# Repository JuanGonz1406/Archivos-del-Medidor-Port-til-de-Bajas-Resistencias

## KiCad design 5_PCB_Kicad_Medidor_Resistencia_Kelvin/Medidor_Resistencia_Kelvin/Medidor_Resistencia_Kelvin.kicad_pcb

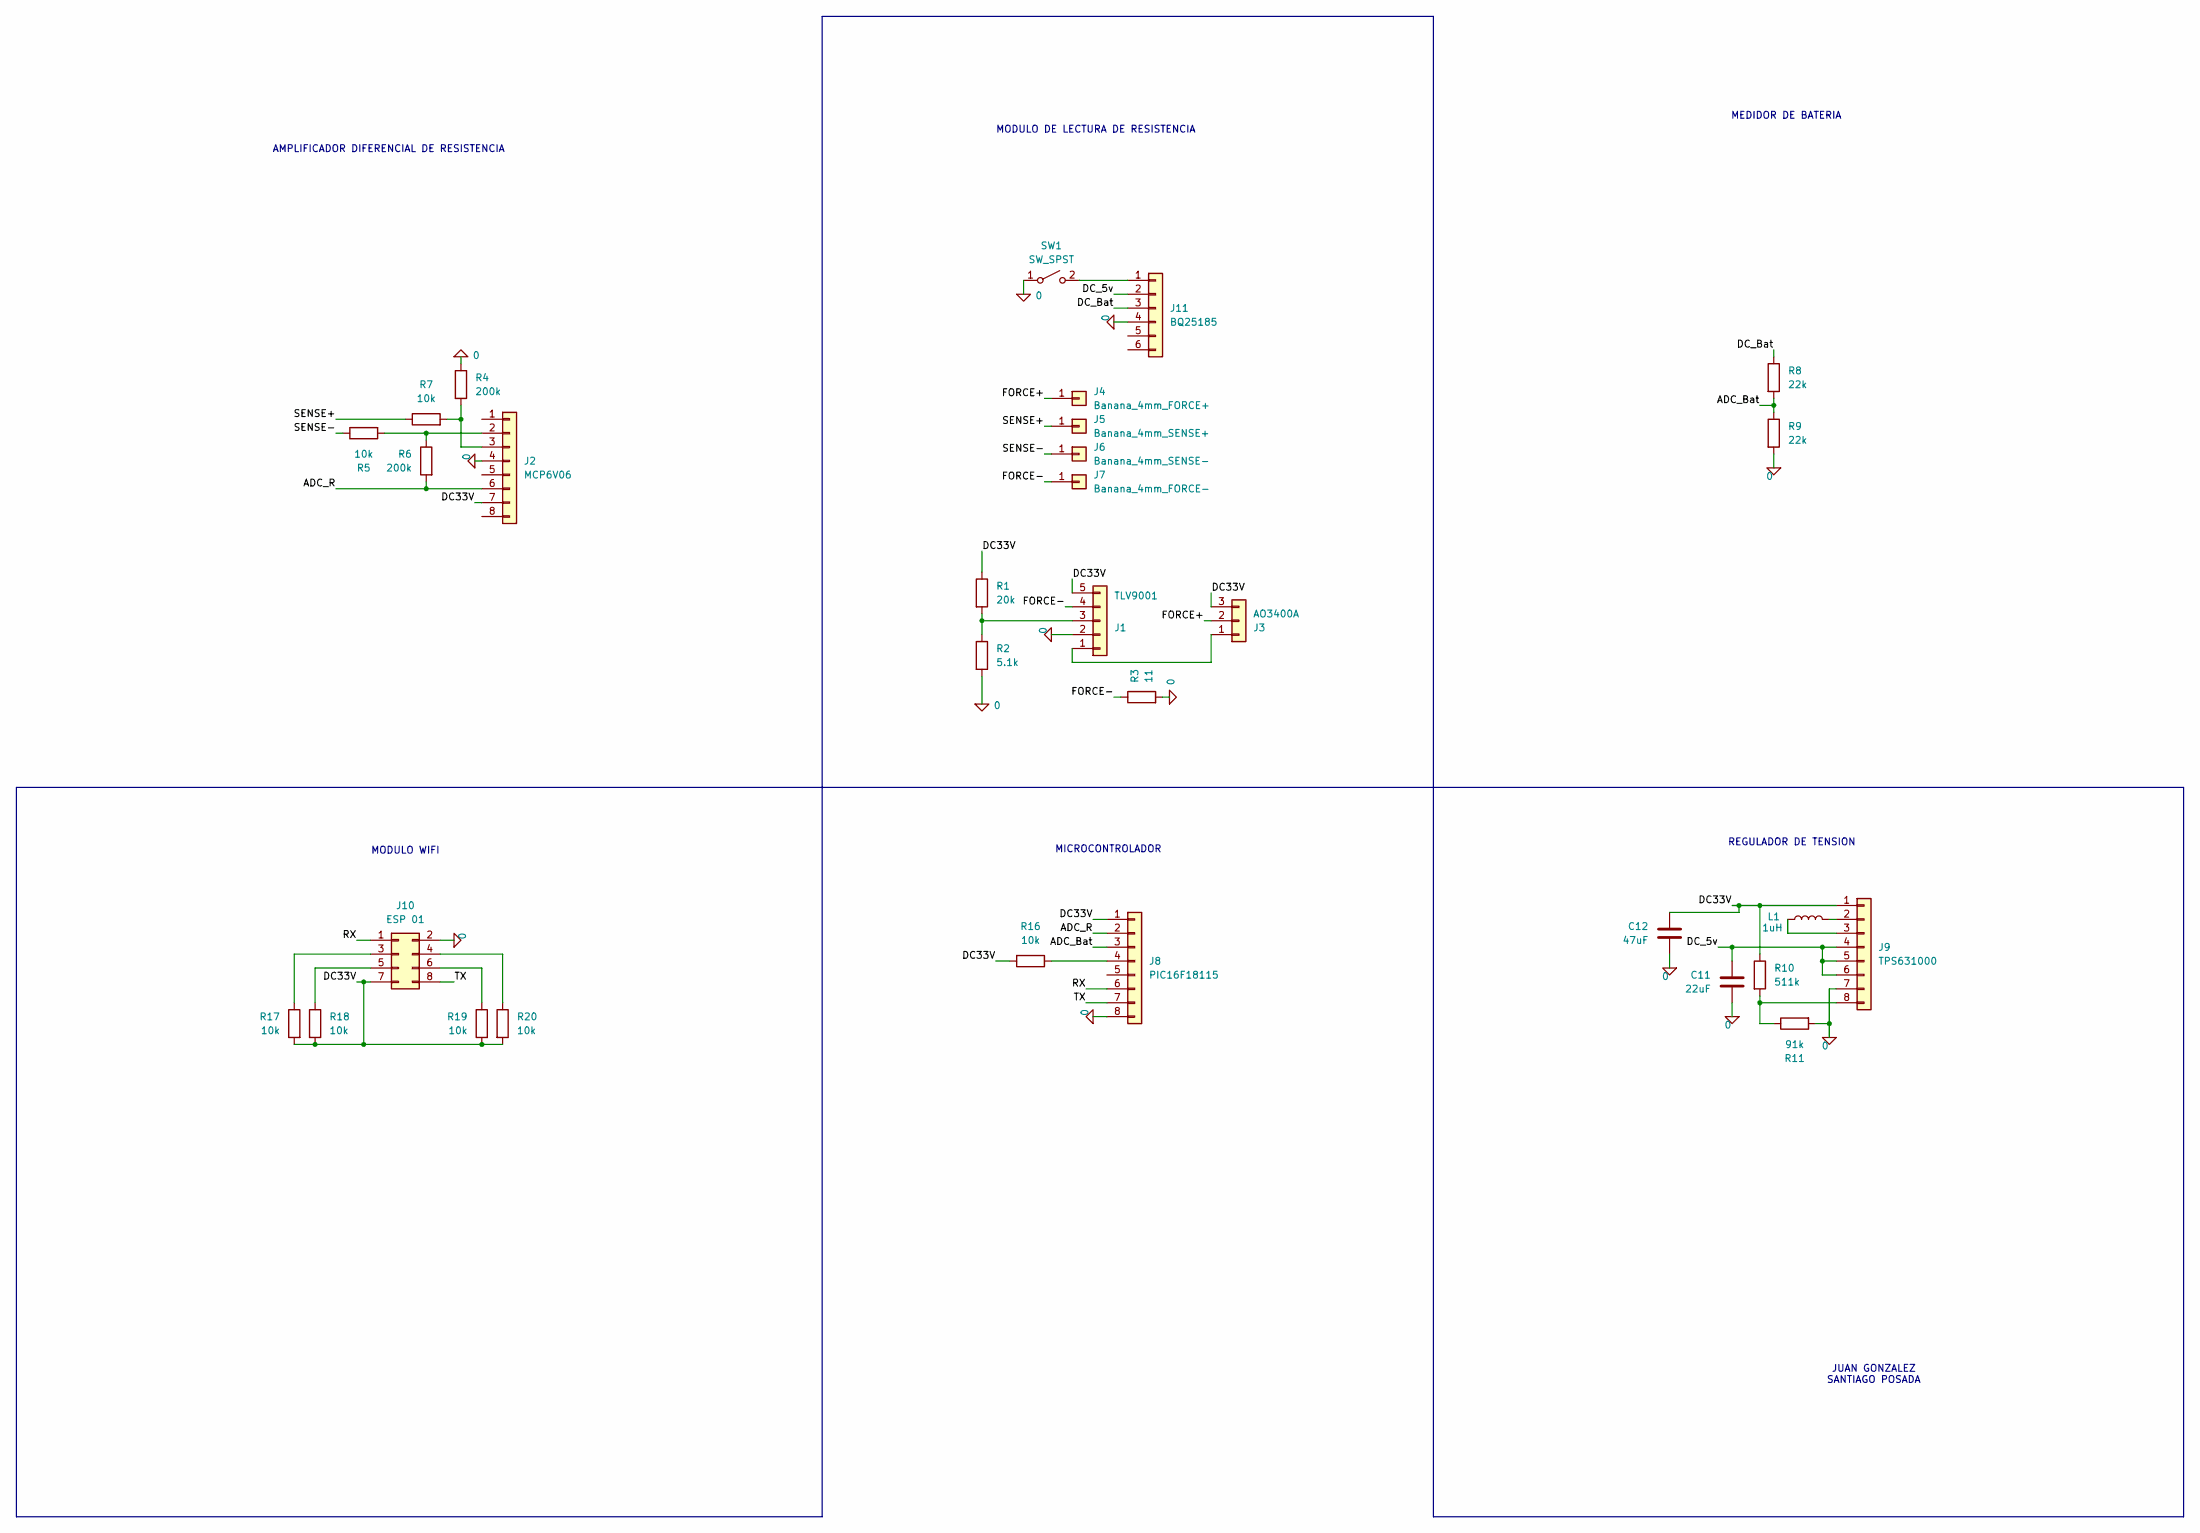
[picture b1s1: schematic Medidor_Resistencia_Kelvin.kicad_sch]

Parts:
C11: 22uF; C_1206_3216Metric
C12: 47uF; C_1206_3216Metric
J1: TLV9001; SOT-23-5
J2: MCP6V06; SOIC-8_3.9x4.9mm_P1.27mm
J3: AO3400A; SOT-23
J4: Banana_4mm_FORCE+; Banana4mm
J5: Banana_4mm_SENSE+; Banana4mm
J6: Banana_4mm_SENSE-; Banana4mm
J7: Banana_4mm_FORCE-; Banana4mm
J8: PIC16F18115; SOIC-8_3.9x4.9mm_P1.27mm
J9: TPS631000; SOT-583-8
J10: ESP 01; PinSocket_2x04_P2.54mm_Vertical
J11: BQ25185; PinHeader_1x06_P2.54mm_Vertical
L1: 1uH; L_Wuerth_MAPI-2512
R1: 20k; R_1206_3216Metric
R2: 5.1k; R_1206_3216Metric
R3: 11; R_1206_3216Metric
R4, R6: 200k; R_1206_3216Metric
R5, R7, R16, R17, R18, R19, R20: 10k; R_1206_3216Metric
R8, R9: 22k; R_1206_3216Metric
R10: 511k; R_1206_3216Metric
R11: 91k; R_1206_3216Metric
SW1: SW_SPST; SW_E-Switch_EG1224_SPDT_Angled

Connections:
0: C11.2, C12.2, J1.2, J2.4, J8.8, J9.7, J10.2, J11.4, R2.2, R3.2, R4.1, R9.2, R11.2, SW1.1 (A)
/ADC_Bat: J8.3, R8.2, R9.1
/ADC_R: J2.6, J8.2, R6.2
/DC33V: C12.1, J1.5, J2.7, J3.3, J8.1, J9.1, J10.7, R1.1, R10.1, R16.2, R17.2, R18.2, R19.2, R20.2
/DC_5v: C11.1, J9.4, J9.5, J9.6, J11.2
/DC_Bat: J11.3, R8.1
/FORCE+: J3.2, J4.1 (Pin_1_1)
/FORCE-: J1.4, J7.1 (Pin_1_1), R3.1
/RX: J8.6, J10.1
/SENSE+: J5.1 (Pin_1_1), R7.1
/SENSE-: J6.1 (Pin_1_1), R5.1
/TX: J8.7, J10.8
unnamed: J1.1, J3.1
unnamed: J1.3, R1.2, R2.1
unnamed: J2.2, R5.2, R6.1
unnamed: J2.3, R4.2, R7.2
unnamed: J8.4, R16.1
unnamed: J9.2, L1.2
unnamed: J9.3, L1.1
unnamed: J9.8, R10.2, R11.1
unnamed: J10.3, R17.1
unnamed: J10.4, R20.1
unnamed: J10.5, R18.1
unnamed: J10.6, R19.1
unnamed: J11.1, SW1.2 (B)

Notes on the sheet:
MEDIDOR DE BATERIA
MICROCONTROLADOR
MODULO WIFI
AMPLIFICADOR DIFERENCIAL DE RESISTENCIA
REGULADOR DE TENSION
MODULO DE LECTURA DE RESISTENCIA
JUAN GONZALEZ SANTIAGO POSADA

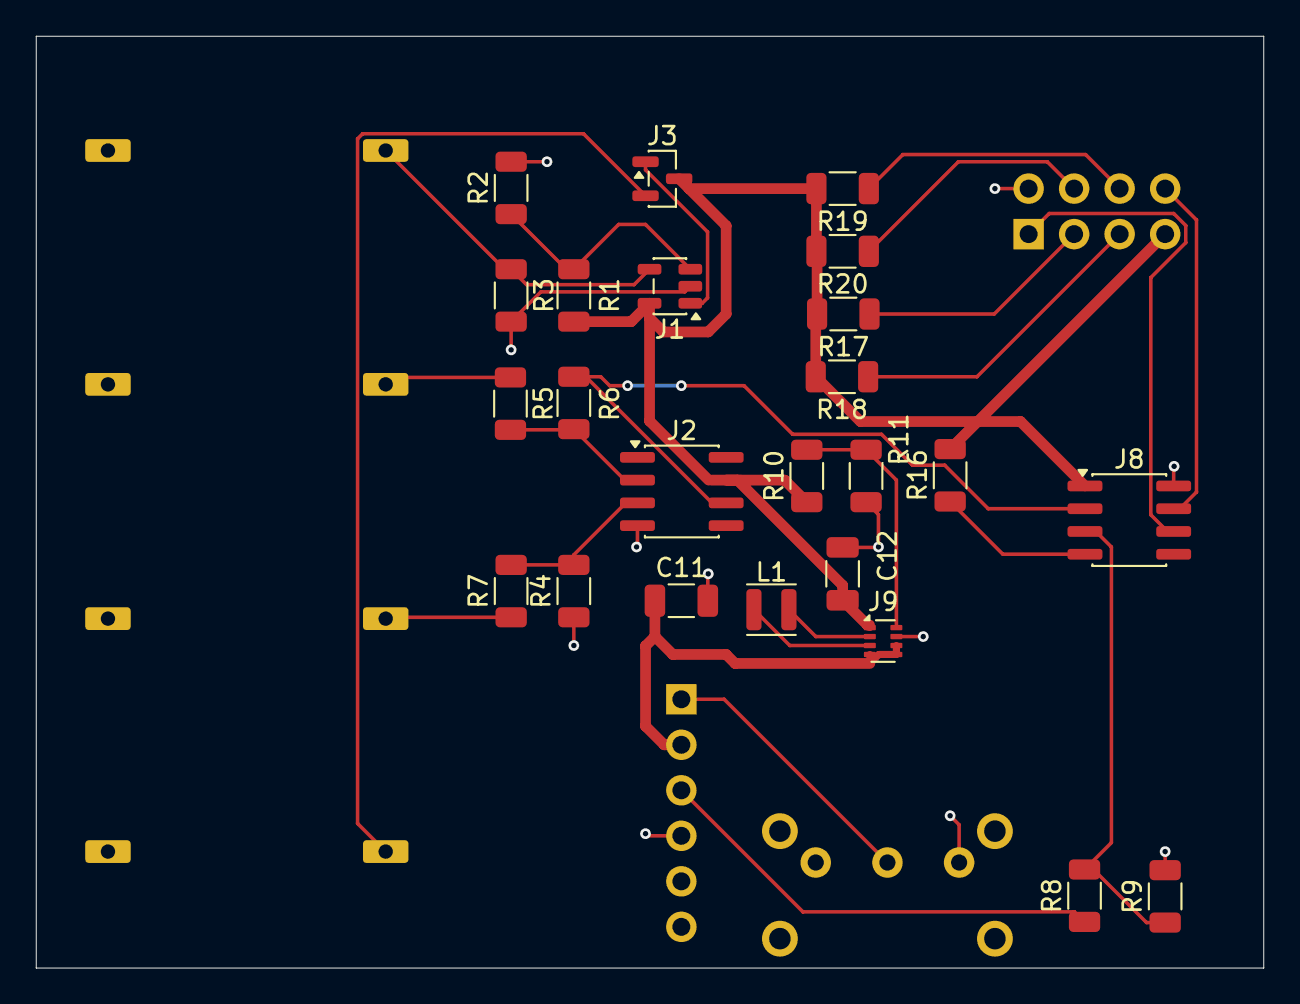
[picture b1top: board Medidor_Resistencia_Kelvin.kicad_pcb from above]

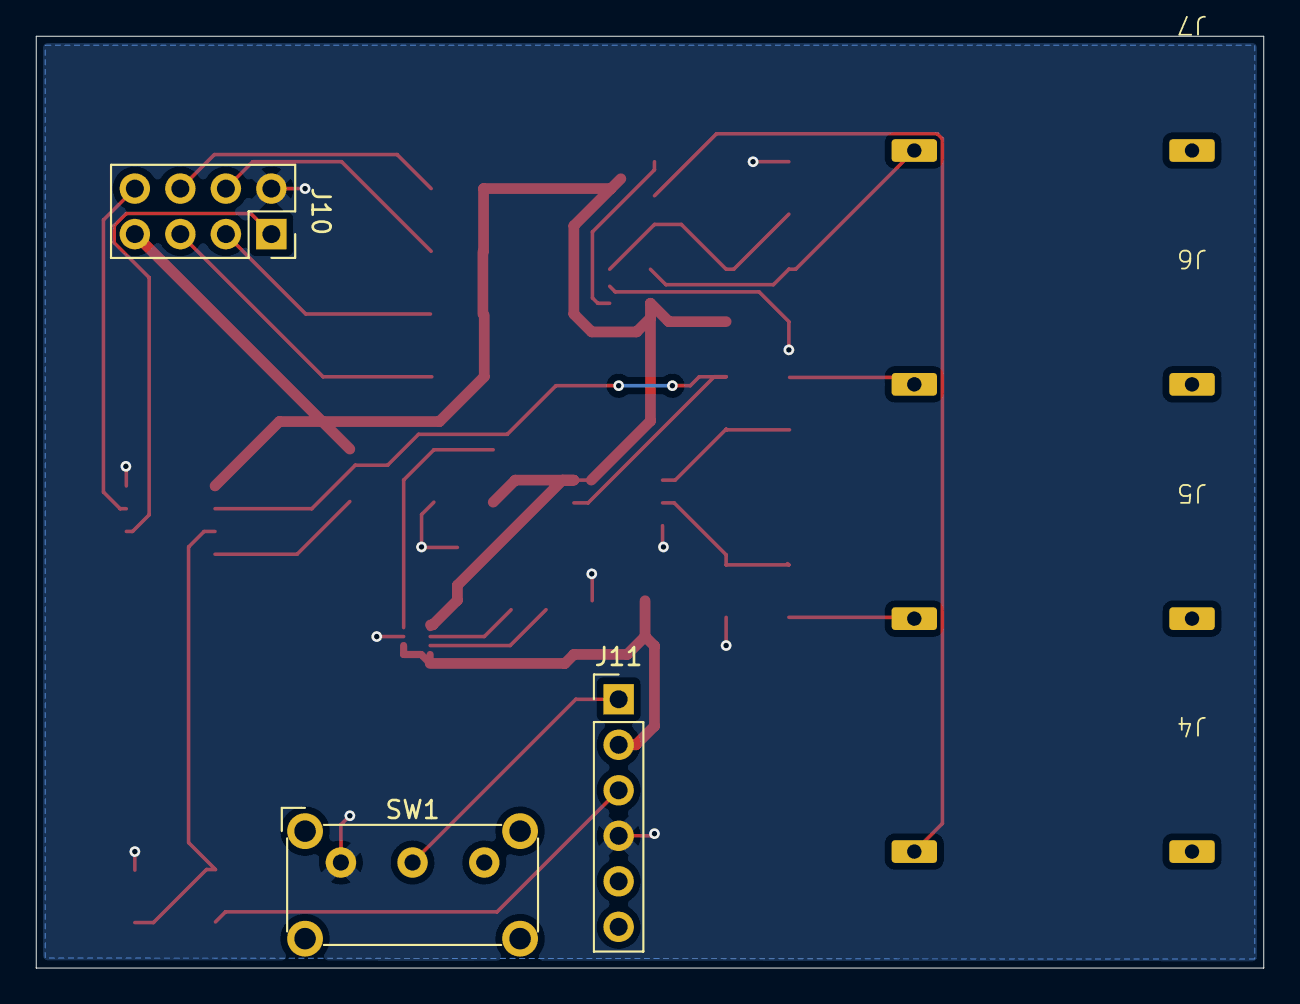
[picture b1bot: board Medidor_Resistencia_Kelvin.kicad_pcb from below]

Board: 2 copper layers, 68.5 x 52.0 mm, 31 parts (7 on the bottom side), 25 nets.
